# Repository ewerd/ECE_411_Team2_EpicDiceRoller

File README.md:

# ECE_411_Team2_EpicDiceRoller
ECE 411 Team 2 Practicum Project

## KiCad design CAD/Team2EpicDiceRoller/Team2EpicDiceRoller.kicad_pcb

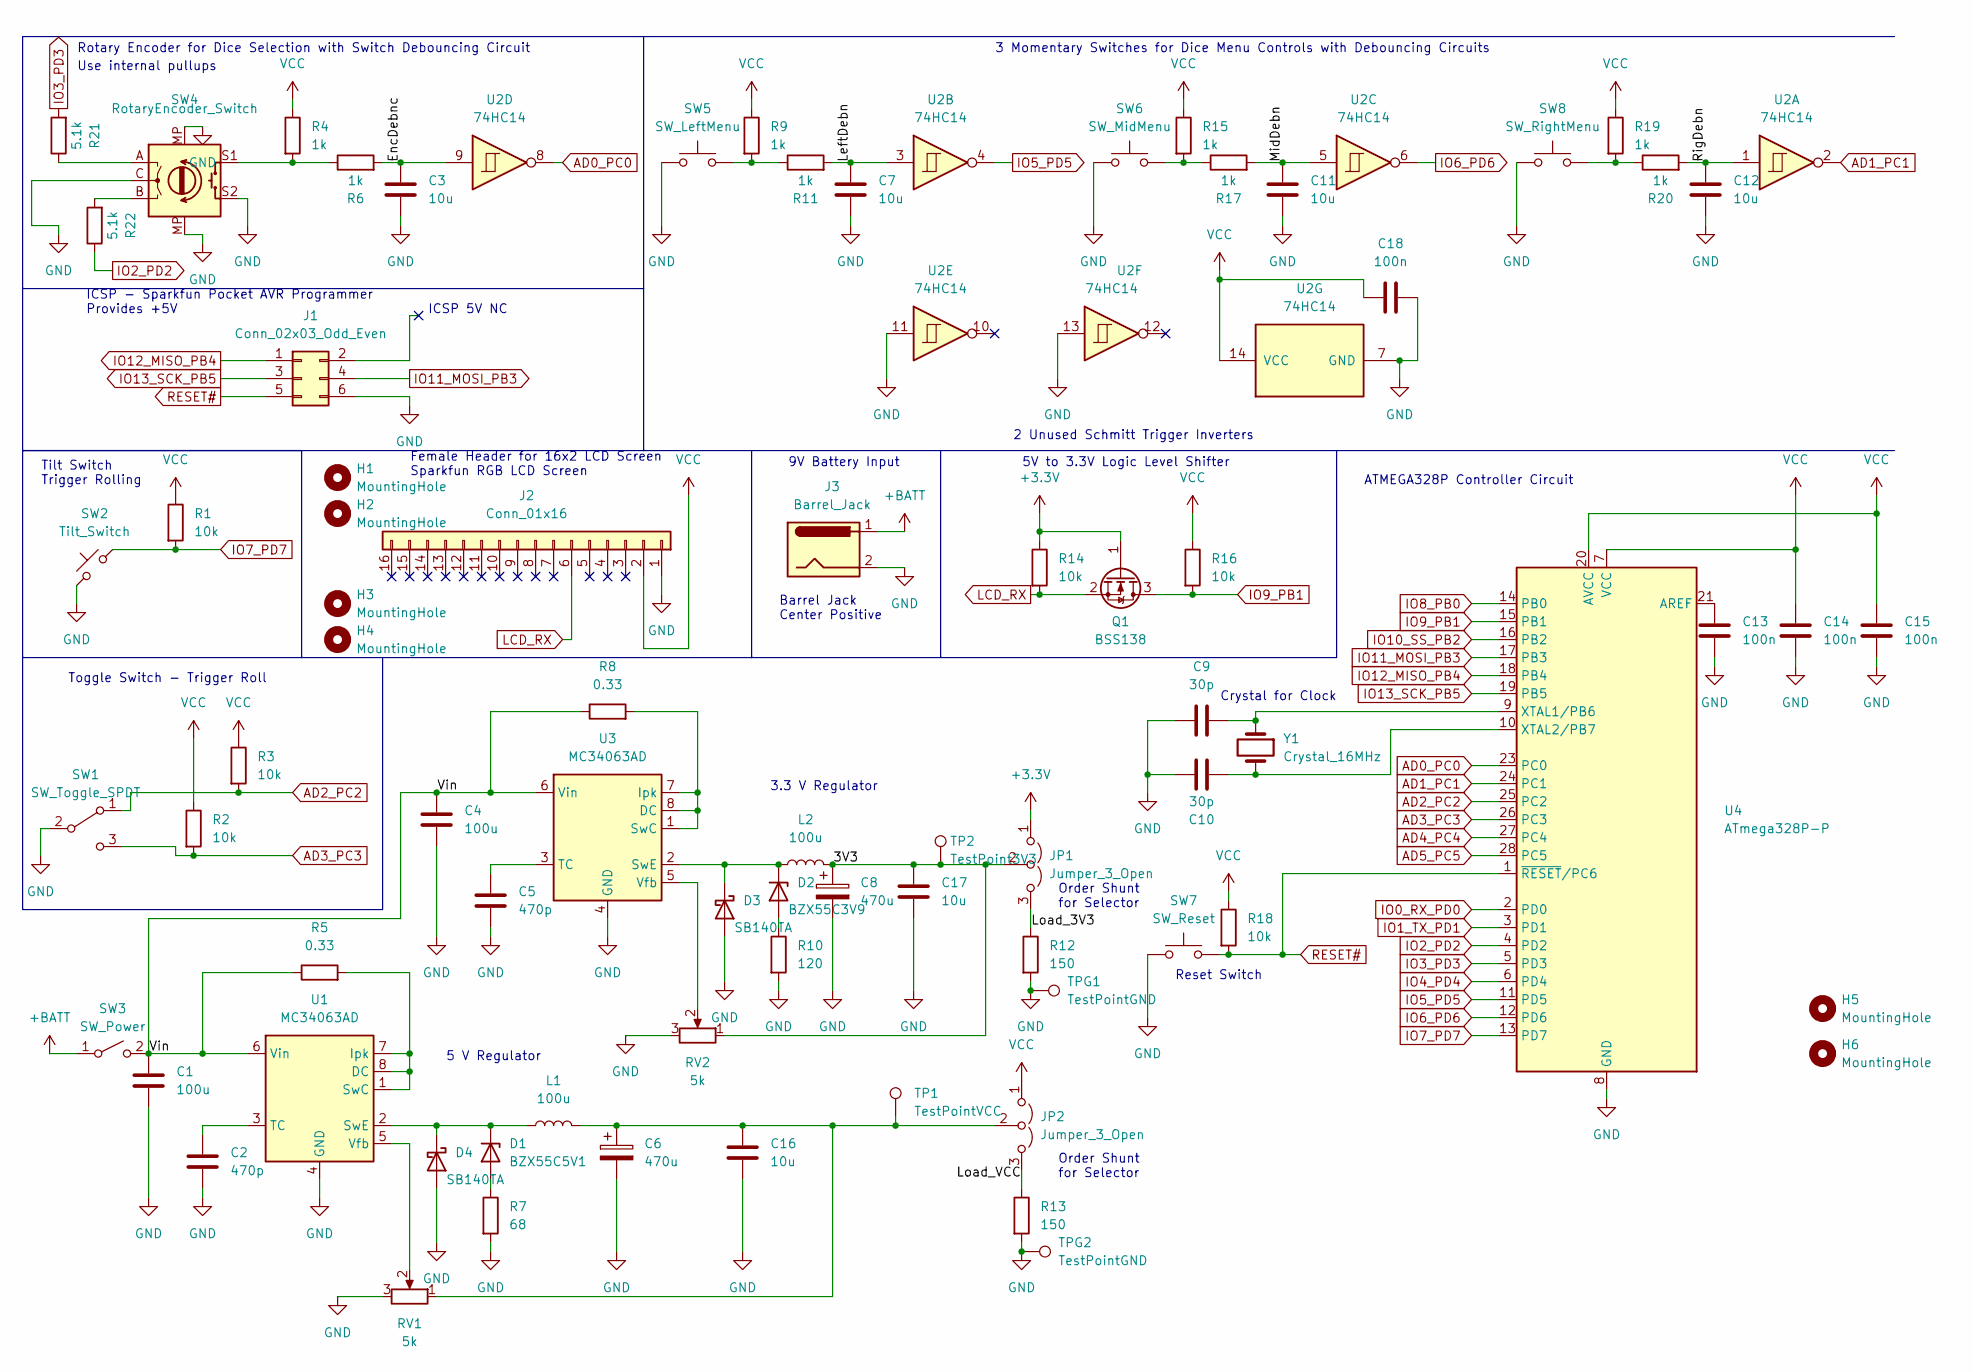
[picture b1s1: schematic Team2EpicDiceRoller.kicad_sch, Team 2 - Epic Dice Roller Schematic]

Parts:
C1, C4: 100u; C_1206_3216Metric_Pad1.33x1.80mm_HandSolder
C2, C5: 470p; C_1206_3216Metric_Pad1.33x1.80mm_HandSolder
C3, C7, C11, C12, C16, C17: 10u; C_1206_3216Metric_Pad1.33x1.80mm_HandSolder
C6, C8: 470u; CP_Radial_D6.3mm_P2.50mm
C9, C10: 30p; C_1206_3216Metric_Pad1.33x1.80mm_HandSolder
C13, C14, C15, C18: 100n; C_1206_3216Metric_Pad1.33x1.80mm_HandSolder
D1: BZX55C5V1; D_DO-35_SOD27_P7.62mm_Horizontal
D2: BZX55C3V9; D_DO-35_SOD27_P7.62mm_Horizontal
D3, D4: SB140TA; D_DO-41_SOD81_P10.16mm_Horizontal
H1, H2, H3, H4, H5, H6: MountingHole; MountingHole_3.2mm_M3
J1: Conn_02x03_Odd_Even; PinSocket_2x03_P2.54mm_Vertical
J2: Conn_01x16; PinSocket_1x16_P2.54mm_Vertical_LCD
J3: Barrel_Jack; BarrelJack_CUI_PJ-037A_Horizontal
JP1, JP2: Jumper_3_Open; PinHeader_1x03_P2.54mm_Vertical
L1, L2: 100u; L_1210_3225Metric_Pad1.42x2.65mm_HandSolder
Q1: BSS138; SOT-323_SC-70_Handsoldering
R1, R2, R3, R14, R16, R18: 10k; R_1206_3216Metric_Pad1.30x1.75mm_HandSolder
R4, R6, R9, R11, R15, R17, R19, R20: 1k; R_1206_3216Metric_Pad1.30x1.75mm_HandSolder
R5, R8: 0.33; R_1206_3216Metric_Pad1.30x1.75mm_HandSolder
R7: 68; R_1206_3216Metric_Pad1.30x1.75mm_HandSolder
R10: 120; R_1206_3216Metric_Pad1.30x1.75mm_HandSolder
R12, R13: 150; R_2512_6332Metric_Pad1.40x3.35mm_HandSolder
R21, R22: 5.1k; R_1206_3216Metric_Pad1.30x1.75mm_HandSolder
RV1, RV2: 5k; TRIM_TC33X-2-502E
SW1: SW_Toggle_SPDT; GoldSun_MTS103_Mini_Toggle_Switch
SW2: Tilt_Switch; PinHeader_1x02_P2.54mm_Vertical
SW3: SW_Power; SW_GF-123-0054
SW4: RotaryEncoder_Switch; RotaryEncoder_Alps_EC11E-Switch_Vertical_H20mm
SW5: SW_LeftMenu; SW_PUSH_6mm_H5mm
SW6: SW_MidMenu; SW_PUSH_6mm_H5mm
SW7: SW_Reset; SW_PUSH_6mm_H5mm
SW8: SW_RightMenu; SW_PUSH_6mm_H5mm
TP1: TestPointVCC; TestPoint_Pad_D2.0mm
TP2: TestPoint3V3; TestPoint_Pad_D2.0mm
TPG1, TPG2: TestPointGND; TestPoint_Pad_D2.0mm
U1, U3: MC34063AD; SOIC-8_3.9x4.9mm_P1.27mm
U2: 74HC14; SOIC-14_3.9x8.7mm_P1.27mm
U4: ATmega328P-P; DIP-28_W7.62mm
Y1: Crystal_16MHz; Crystal_HC49-4H_Vertical

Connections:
+3V3: JP1.1 (A), Q1.1 (G), R14.1
+BATT: J3.1, SW3.1 (A)
/3V3: C8.1, C17.1, JP1.2 (C), L2.2, RV2.1, TP2.1
/EncDebnc: C3.1, R6.2, U2.9
/LeftDebn: C7.1, R11.2, U2.3
/Load_3V3: JP1.3 (B), R12.1
/Load_VCC: JP2.3 (B), R13.1
/MidDebn: C11.1, R17.2, U2.5
/RigDebn: C12.1, R20.2, U2.1
/Vin: C1.1, C4.1, R5.1, R8.1, SW3.2 (B), U1.6 (Vin), U3.6 (Vin)
AD0_PC0: U2.8, U4.23 (PC0)
AD1_PC1: U2.2, U4.24 (PC1)
AD2_PC2: R3.2, SW1.1 (A), U4.25 (PC2)
AD3_PC3: R2.2, SW1.3 (C), U4.26 (PC3)
AD4_PC4: U4.27 (PC4)
AD5_PC5: U4.28 (PC5)
GND: C1.2, C2.2, C3.2, C4.2, C5.2, C6.2, C7.2, C8.2, C9.1, C10.1, C11.2, C12.2, C13.1, C14.1, C15.1, C16.2, C17.2, C18.1, D3.2 (A), D4.2 (A), J1.6, J2.1, J3.2, R7.2, R10.2, R12.2, R13.2, RV1.3, RV2.3, SW1.2 (B), SW2.2, SW4.C, SW4.MP, SW4.S2, SW5.1, SW6.1, SW7.1, SW8.1, TPG1.1, TPG2.1, U1.4 (GND), U2.7 (GND), U2.11, U2.13, U3.4 (GND), U4.8 (GND), U4.22 (GND)
IO0_RX_PD0: U4.2 (PD0)
IO1_TX_PD1: U4.3 (PD1)
IO2_PD2: R22.1, U4.4 (PD2)
IO3_PD3: R21.2, U4.5 (PD3)
IO4_PD4: U4.6 (PD4)
IO5_PD5: U2.4, U4.11 (PD5)
IO6_PD6: U2.6, U4.12 (PD6)
IO7_PD7: R1.2, SW2.1, U4.13 (PD7)
IO8_PB0: U4.14 (PB0)
IO9_PB1: Q1.3 (D), R16.2, U4.15 (PB1)
IO10_SS_PB2: U4.16 (PB2)
IO11_MOSI_PB3: J1.4, U4.17 (PB3)
IO12_MISO_PB4: J1.1, U4.18 (PB4)
IO13_SCK_PB5: J1.3, U4.19 (PB5)
LCD_RX: J2.6, Q1.2 (S), R14.2
unnamed: C2.1, U1.3 (TC)
unnamed: C5.1, U3.3 (TC)
unnamed: C9.2, U4.9 (XTAL1/PB6), Y1.1
unnamed: C10.2, U4.10 (XTAL2/PB7), Y1.2
unnamed: C13.2, U4.21 (AREF)
unnamed: C6.1, C16.1, JP2.2 (C), L1.2, RV1.1, TP1.1
unnamed: D1.1 (K), D4.1 (K), L1.1, U1.2 (SwE)
unnamed: D1.2 (A), R7.1
unnamed: D2.1 (K), D3.1 (K), L2.1, U3.2 (SwE)
unnamed: D2.2 (A), R10.1
unnamed: R4.2, R6.1, SW4.S1
unnamed: R5.2, U1.1 (SwC), U1.7 (Ipk), U1.8 (DC)
unnamed: R8.2, U3.1 (SwC), U3.7 (Ipk), U3.8 (DC)
unnamed: R9.2, R11.1, SW5.2
unnamed: R15.2, R17.1, SW6.2
unnamed: R19.2, R20.1, SW8.2
unnamed: R21.1, SW4.A
unnamed: R22.2, SW4.B
unnamed: RV1.2, U1.5 (Vfb)
unnamed: RV2.2, U3.5 (Vfb)
RESET#: J1.5, R18.2, SW7.2, U4.1 (~RESET/PC6)
VCC: C14.2, C15.2, C18.2, J2.2, JP2.1 (A), R1.1, R2.1, R3.1, R4.1, R9.1, R15.1, R16.1, R18.1, R19.1, U2.14 (VCC), U4.7 (VCC), U4.20 (AVCC)

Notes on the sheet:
Tilt Switch Trigger Rolling
Toggle Switch - Trigger Roll
Rotary Encoder for Dice Selection with Switch Debouncing Circuit
Use internal pullups
ICSP - Sparkfun Pocket AVR Programmer Provides +5V
Female Header for 16x2 LCD Screen Sparkfun RGB LCD Screen
ICSP 5V NC
5 V Regulator
3.3 V Regulator
Barrel Jack Center Positive
9V Battery Input
3 Momentary Switches for Dice Menu Controls with Debouncing Circuits
2 Unused Schmitt Trigger Inverters
5V to 3.3V Logic Level Shifter
Order Shunt for Selector
Reset Switch
Crystal for Clock
ATMEGA328P Controller Circuit

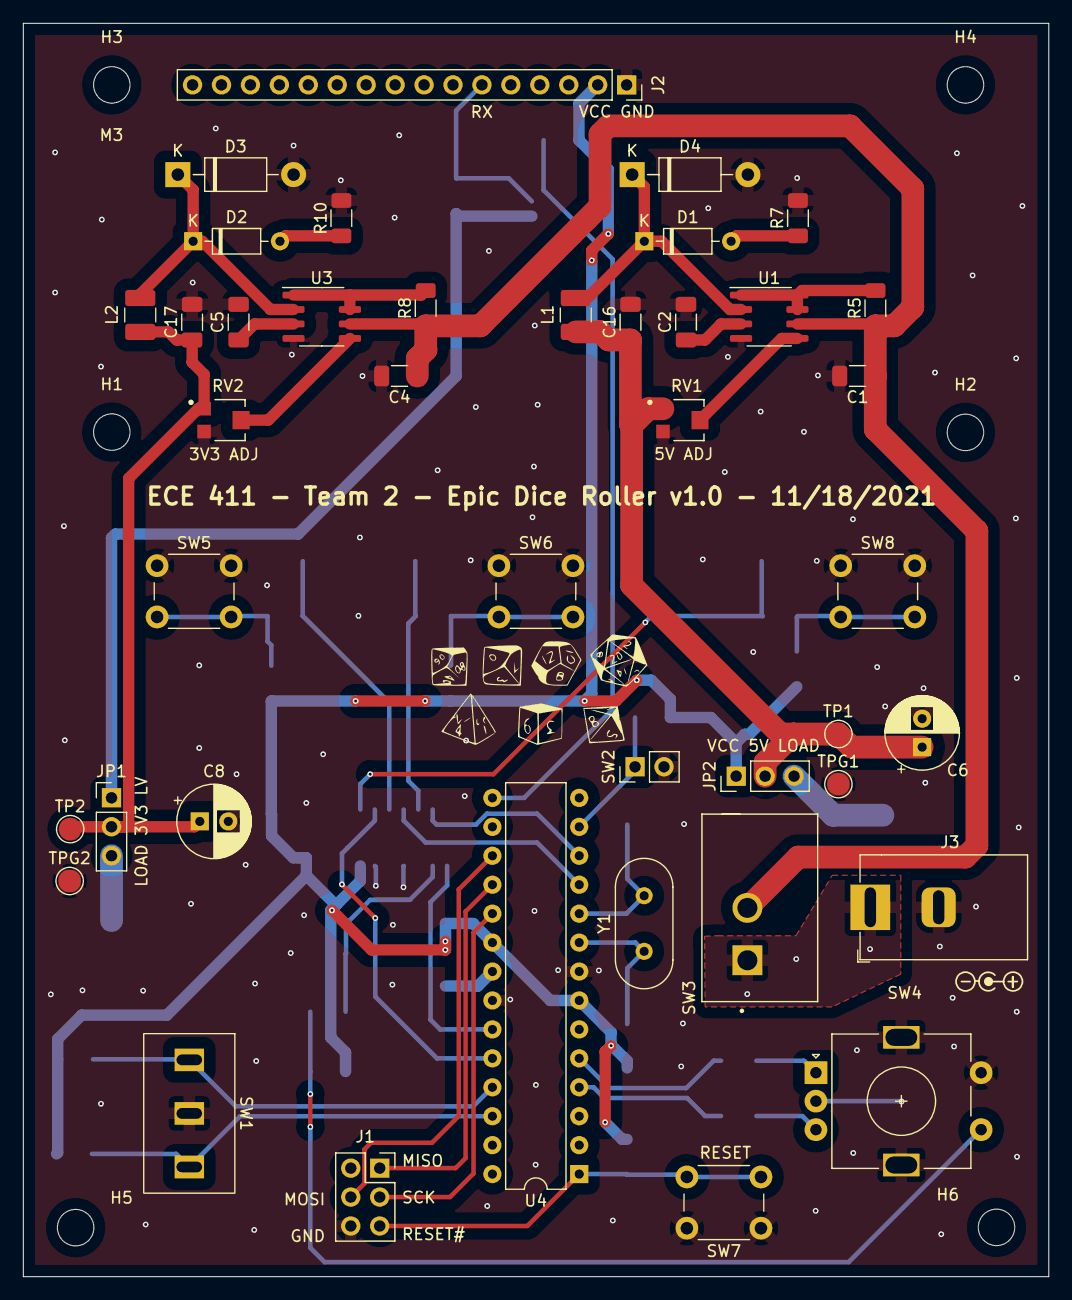
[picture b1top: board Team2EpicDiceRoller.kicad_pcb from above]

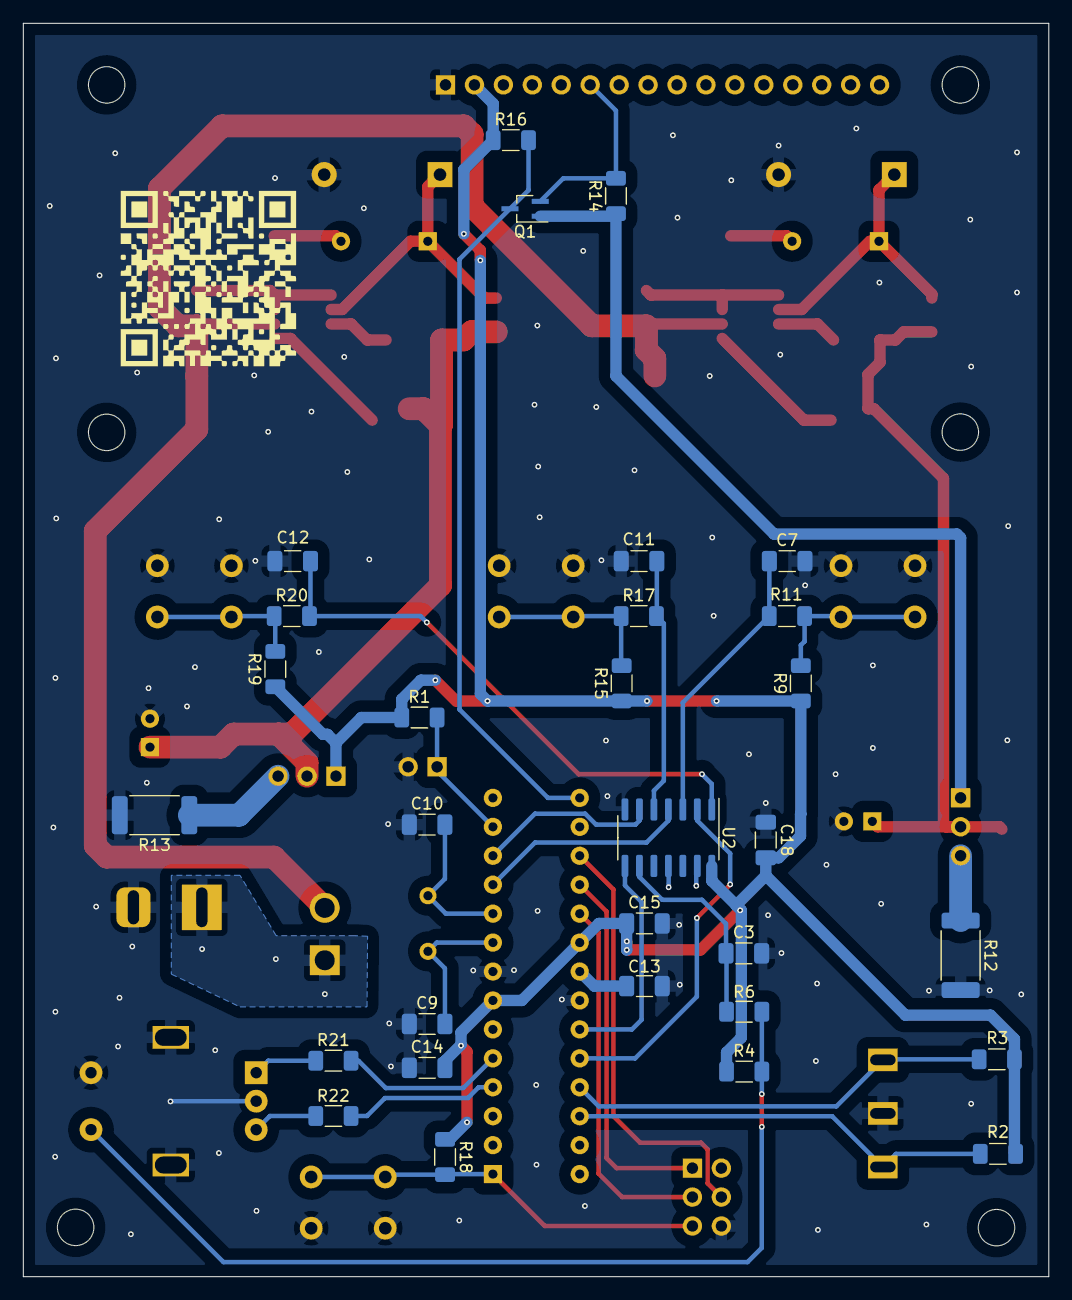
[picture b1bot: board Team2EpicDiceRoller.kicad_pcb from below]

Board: 2 copper layers, 90.0 x 110.0 mm, 77 parts (30 on the bottom side), 47 nets.

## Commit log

2021-10-21 added Product Design Specification
2021-10-21 Changed hyphens to bullets
2021-10-21 Added text to the image description.
2021-10-21 Update Product_Design_Specification.md
    Added two new specs related to original practicum requirements
2021-10-21 .DS_Store banished!
2021-10-21 Update
    PDF file changes and emails added for project contributors.
2021-10-21 update
    update on pdf and emails again
2021-10-21 rearranging text
2021-10-21 fixed line spacing
2021-10-27 Updated the voltage divider on BJT base
2021-10-28 Added initial schematic for the IO. Also contains basic circuitry for the controller
2021-10-28 name correction
2021-10-28 added tilt photo
2021-10-28 picture of basic breadboarding prototype
2021-10-28 PS Measurements
2021-10-28 Week 5 Update
2021-11-04 Add combined KiCAD schematic
2021-11-04 Project Gantt Schedule
    Schedule link found here:
    https://app.smartsheet.com/sheets/wM9WRRxg5V49g2pfQhJVrqfWJ6gcW9cvgw8FcqF1
2021-11-08 Added Subsystems to CAD folder
2021-11-08 Finished moving files and added current KiCAD schematic
2021-11-08 removed extranneous files from CAD backups
2021-11-10 Voltage regulator redesign
2021-11-10 Added switch and calibration jumper
2021-11-10 Added power supply circuit, barrel jack, logic level shifter
2021-11-10 Updated schematic
2021-11-11 added footprints for electrolytic capacitor
2021-11-11 updated zener diodes and resistor values
2021-11-11 added testpoint footprints
2021-11-11 Update block diagrams
2021-11-11 Initial routing - done poorly, need to update power switch footprint
2021-11-11 Removed old backups
2021-11-11 Initial functional decomp
2021-11-15 Added renamed backup of unrouted PCB
2021-11-15 Added no traces version here
2021-11-15 Found better way, just global delete traces and zones
2021-11-16 Updated schematic to remove traces and update the footprints
2021-11-16 Added mounting holes for the standoffs
2021-11-16 Newer version
2021-11-16 Added cap, moved pots, many changes
2021-11-16 should be good now
2021-11-16 Updated silk screen, ready to route
2021-11-16 Stephens first route
2021-11-16 My cad example
2021-11-16 drew's layout. Still working on ground and final touches
2021-11-16 Removed references to ICSP power supply
2021-11-16 My changes
2021-11-17 minor edits
2021-11-17 Added schottky diode, bypass for schmitt, updated footprints for inductor, fixed level shifter
2021-11-17 missed the level shifter swap fix
2021-11-17 Added note about internal pullups to rotary encoder
2021-11-17 updated layout, footprints look good
2021-11-17 Added 3d models and screen footprint to library folder
2021-11-17 Added design rules example to import before sending to oshpark
2021-11-17 Replaced footprint for 470uF cap
2021-11-18 Added mounting holes, updated general layout of pcb for routing
2021-11-18 Updated pin selections for some of the io so that we can use the screen and the enableinterrupt library at the same time
2021-11-18 Added date to pcb
2021-11-18 Revert "Updated the IO again"
    This reverts commit 80c1a5cda0b79e003991432f29007fe40f1553a5.
2021-11-18 Updated pcb with those changes
2021-11-18 minor changes to text
2021-11-18 flipped a few capacitors
2021-11-18 flipped load capacitors for atmega
2021-11-18 started route
2021-11-18 Revert "flipped load capacitors for atmega"
    This reverts commit 9196768c834bd27db4ced242ad99c57f5f649139.
2021-11-18 route in progress
2021-11-18 Removed extraneous VCC net that caused ghost line between VCC jumper pads
2021-11-18 Found another issue, inductors silkscreen conflicted with capacitors
2021-11-18 Fixed some silkscreen labeling
2021-11-18 added qr code and symbol for power supply jack
2021-11-18 updated pcb and added dice graphic
2021-11-18 Fixed DRC failures, tiny traces, circles on silkscreen holes
2021-11-18 Fixed screen holes, moved them to fab from silk screen
2021-11-18 final adjustments
2021-11-18 Added backups
2021-11-18 Build files and gerbers
2021-11-26 Initial code that connects all of the devices and counts interrupts
2021-11-26 rename to remove version number from code
2021-11-26 updated code into initial working state. Generates interrupts, started with setup state where the user can choose how many and size of dice. Still in progress, but pausing to sleep.
2021-11-27 Basic menu setup, can increment/decrement num dice and use rotary encoder to select the size of dice
2021-11-27 work in progress for rolling aspect
2021-11-29 Added code to main branch
2021-12-02 added test plan
2021-12-04 Rolling now works, and fun additions and settings.
2021-12-05 Most recent, natural 20 and critical 1
2021-12-08 Newest
2021-12-08 Most recent iteration
    -Loaded dice option (Hold board upside down and roll with rotary button)
    -Complete reorganization and modularity implemented
    -No comments still, and one file (out of time to implement multiple files)
    -three methods of rolling
2021-12-09 commenting commenced
2021-12-09 Yahtzee!
2021-12-09 HATZYEE YATHEZE YAZTHEE... forget it
2021-12-09 Dont need this
2021-12-09 Most recent
2021-12-09 reorganized github
2021-12-09 added BOM
2021-12-10 added presentation
